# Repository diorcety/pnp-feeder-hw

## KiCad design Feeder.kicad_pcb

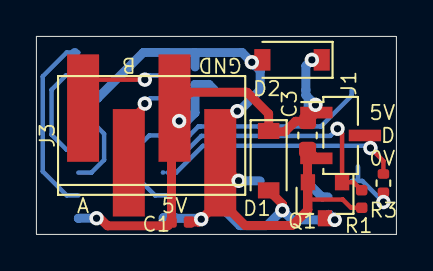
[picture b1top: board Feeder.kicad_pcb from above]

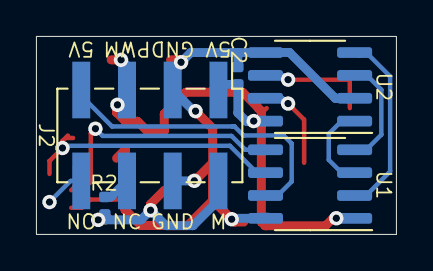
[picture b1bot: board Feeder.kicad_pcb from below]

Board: 2 copper layers, 20.0 x 11.0 mm, 14 parts (5 on the bottom side), 13 nets.

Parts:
C1, C2: 100n; C_0402_1005Metric
C3: 2.2u; C_0603_1608Metric
D1, D2: DSS15UTR; D_SOD-123
J1: UPDI; PinSocket_1x03_P1.27mm_Vertical_SMD_Pin1Left
J2: Internal; PinHeader_2x04_P2.54mm_Vertical_SMD
J3: RS485; 3-647166-4
Q1: 2N7002NXAKR; SOT-23
R1: 47k; R_0402_1005Metric
R2: NP; R_0402_1005Metric
R3: 1k; R_0402_1005Metric
U1: ATtiny402; SOIC-8_3.9x4.9mm_P1.27mm
U2: ST485EBDR; SOIC-8_3.9x4.9mm_P1.27mm

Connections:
+5V: C1.1, C2.1, C3.1, D1.1, D2.1, J1.1, J2.1, J2.5, J3.3, U1.1, U2.8
/A: J3.1, U2.6
/B: J3.2, U2.7
/FEEDBACK: J1.2, R3.1, U1.6
/MOTOR: Q1.1, R1.1, U1.5
/PWM: J2.7, U1.7
GND: C1.2, C2.2, C3.2, D2.2, J1.3, J2.3, J2.4, J3.4, Q1.2, R1.2, U1.8, U2.2, U2.5
unnamed: D1.2, J2.2, Q1.3, R2.1
unnamed: J2.6, R2.2
unnamed: J2.8, R3.2
unnamed: U1.2, U2.4
unnamed: U1.3, U2.1
unnamed: U1.4, U2.3

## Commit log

2021-03-03 Add missing files
2021-03-14 Fix ATTiny402-SS part reference
2021-05-29 Invert Motor and Feedback: Allow to use UPDI pin always as input and may avoid damaged IC
